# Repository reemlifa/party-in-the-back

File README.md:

# Bob the Minion: Business in the Front, Party in the Back!

## Description
---
a simple minion PCB with eyes that light up when you press the button!

## BOM
---
* 1 Battery Holder 
* 1 Push button
* 2 47Ω Resistors
* 2 LEDs

Made by `@reem` on slack :) 

## Schematic View
---

## PCB Editor View
---

## 3D View
---
Front: 

Back:

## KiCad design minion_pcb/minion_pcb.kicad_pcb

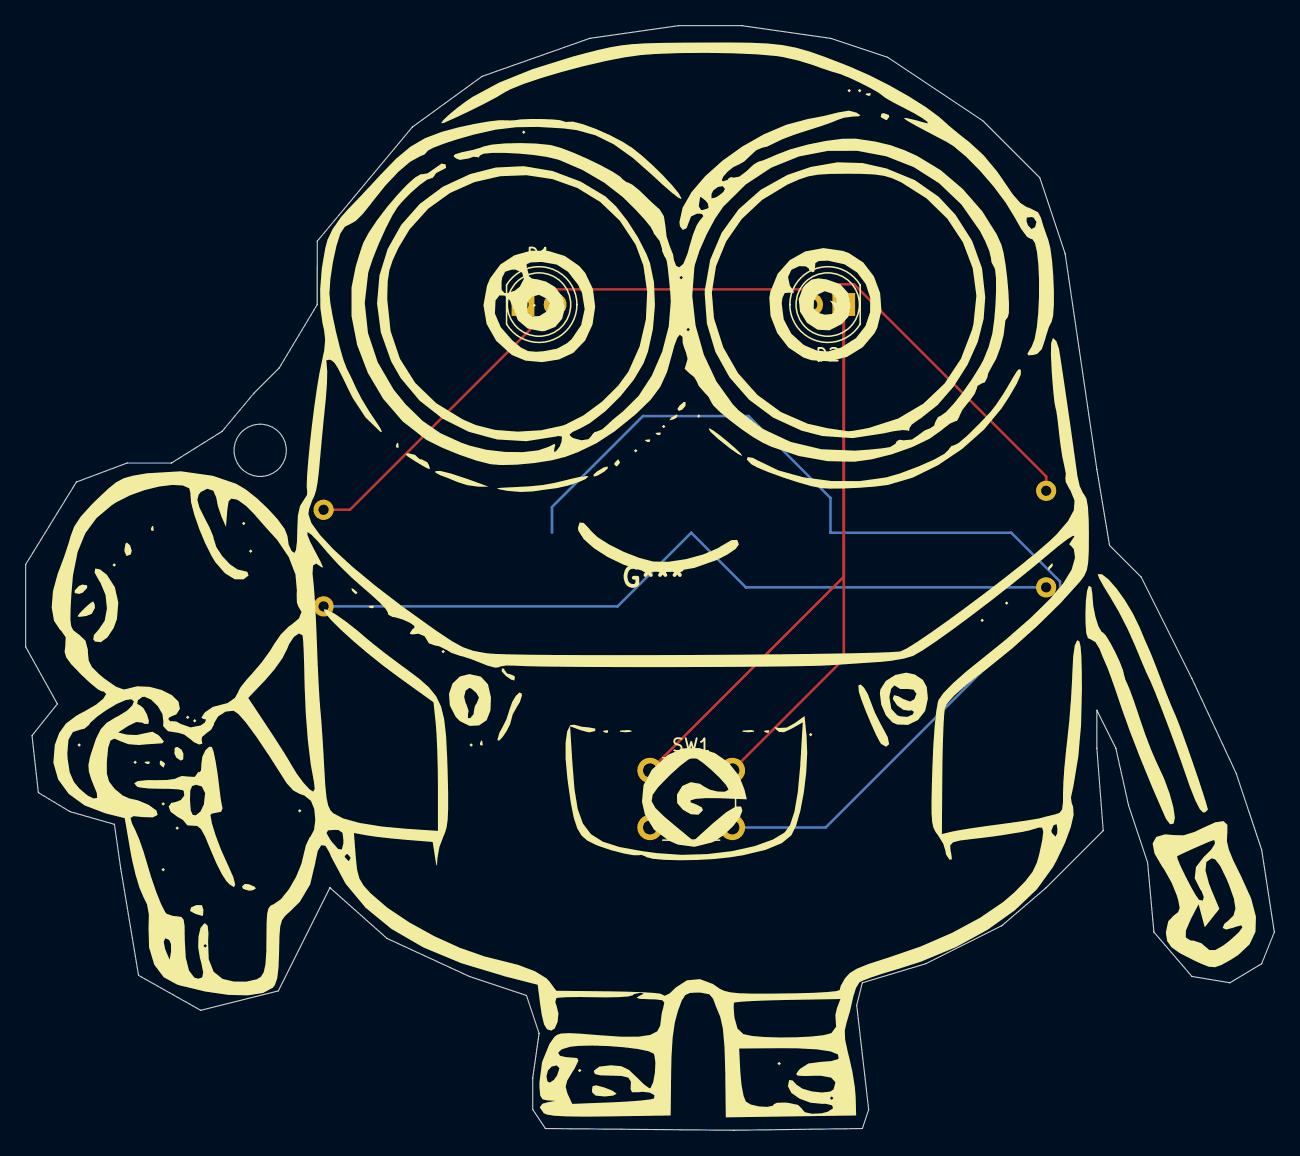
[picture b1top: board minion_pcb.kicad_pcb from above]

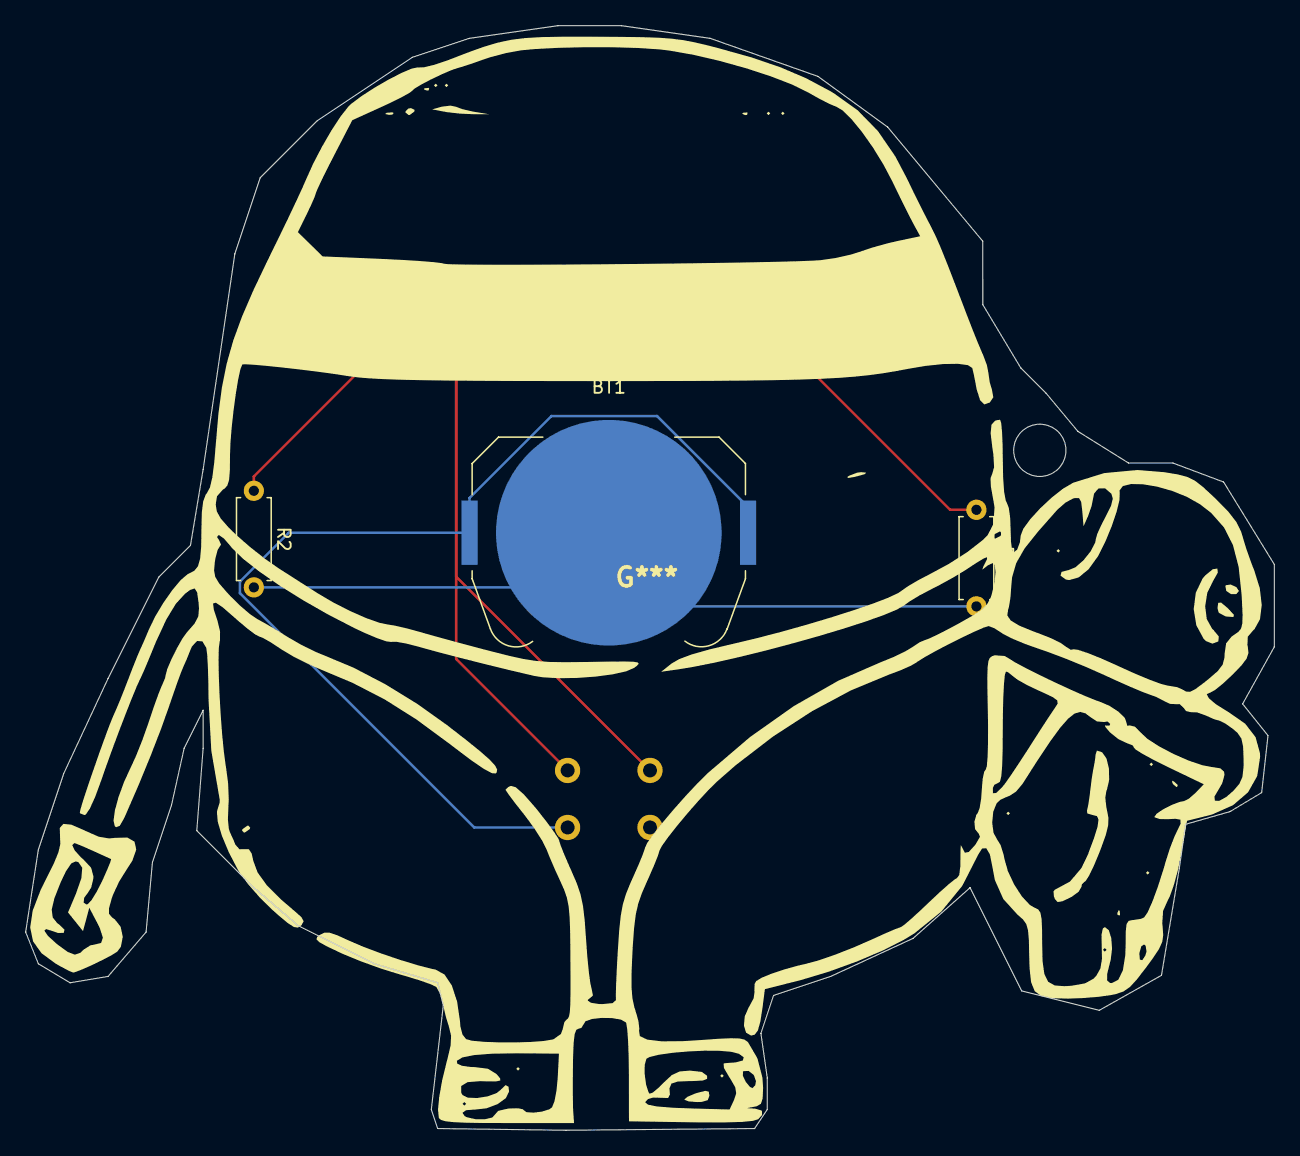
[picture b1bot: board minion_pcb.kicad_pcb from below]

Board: 2 copper layers, 98.5 x 87.1 mm, 6 parts (3 on the bottom side), 5 nets.

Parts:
BT1: Battery; BatteryHolder_Keystone_3034_1x20mm
D1, D2: LED; LED_D5.0mm
R1, R2: 47Ω; R_Axial_DIN0207_L6.3mm_D2.5mm_P7.62mm_Horizontal
SW1: SW_Push; SW_PUSH_6mm

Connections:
GND: BT1.2 (-), R1.2, R2.2
unnamed: BT1.1 (+), SW1.2
unnamed: D1.2 (A), R1.1
unnamed: D1.1 (K), D2.1 (K), SW1.1
unnamed: D2.2 (A), R2.1

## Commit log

2025-05-22 added kicad files
2025-05-24 i forgot to switch the leds :skull:
